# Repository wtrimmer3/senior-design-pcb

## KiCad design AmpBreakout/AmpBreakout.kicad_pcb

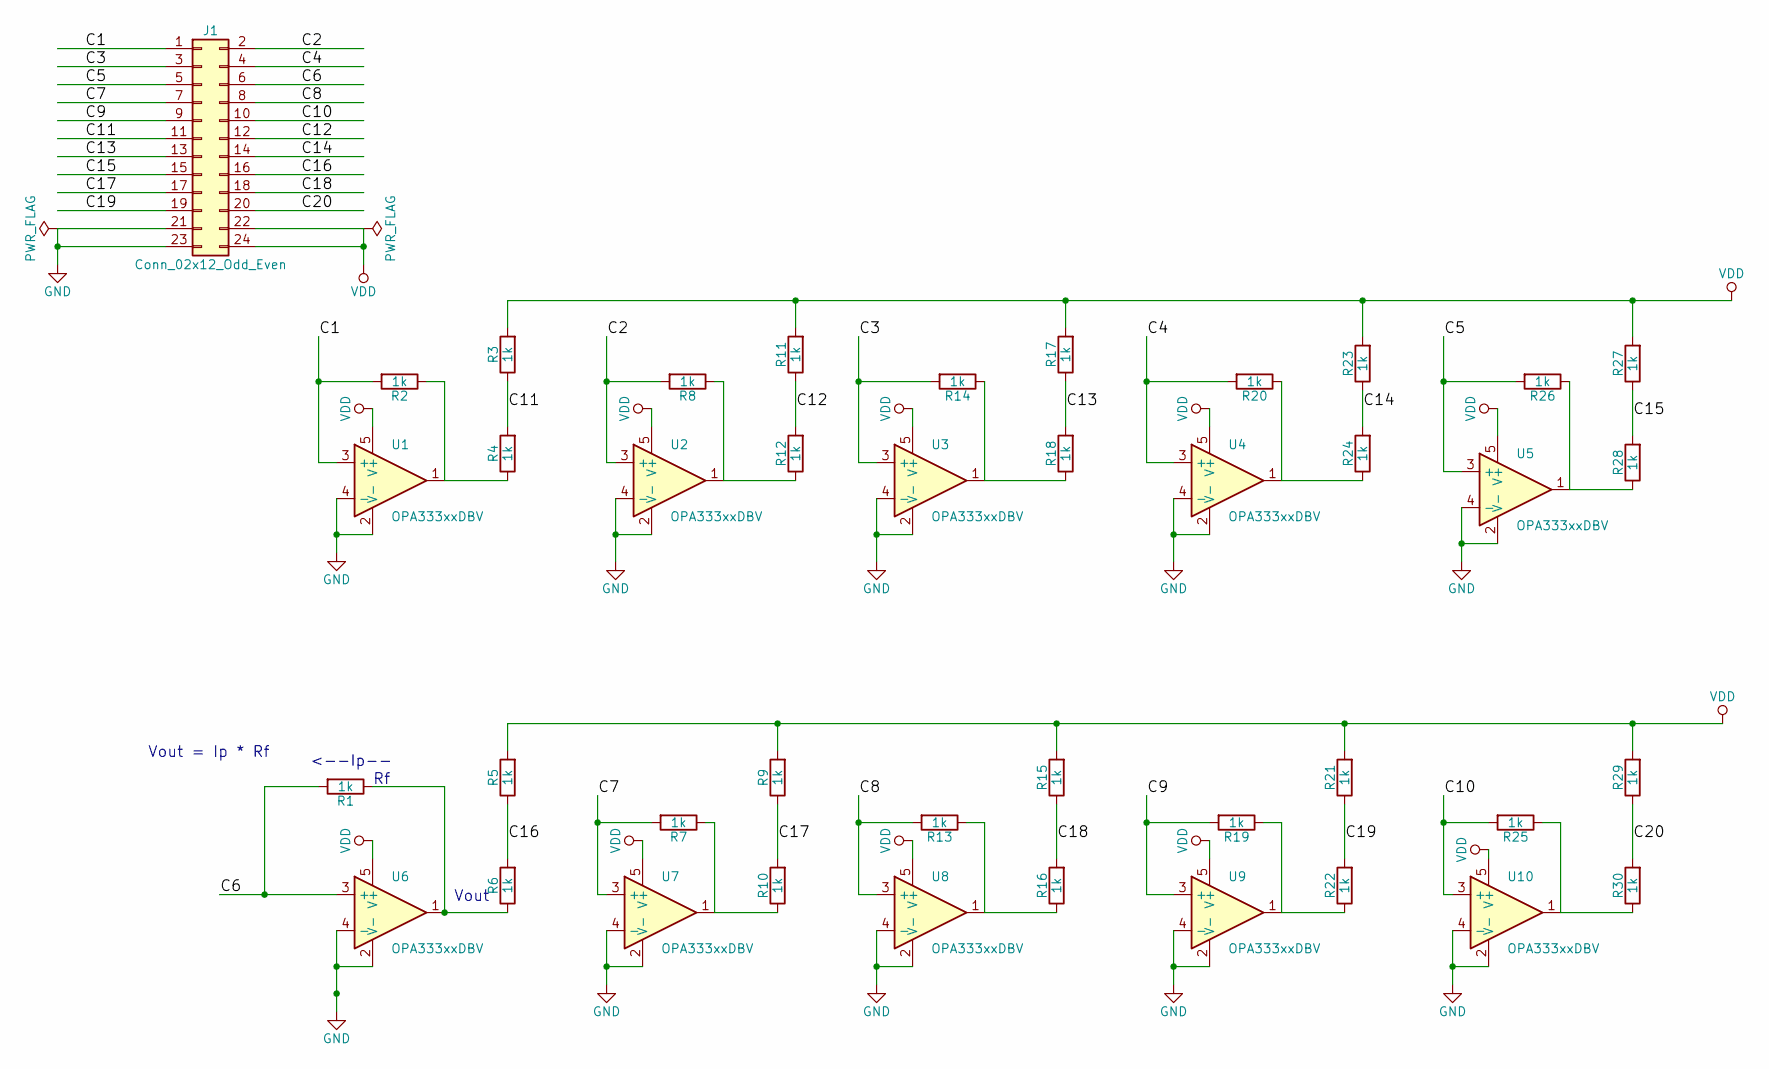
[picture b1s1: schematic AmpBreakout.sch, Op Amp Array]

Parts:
J1: Conn_02x12_Odd_Even; Pin_Header_Straight_2x12_Pitch1.00mm
R1, R2, R3, R4, R5, R6, R7, R8, R9, R10, R11, R12, R13, R14, R15, R16, R17, R18, R19, R20, R21, R22, R23, R24, R25, R26, R27, R28, R29, R30: 1k; R_1206
U1, U2, U3, U4, U5, U6, U7, U8, U9, U10: OPA333xxDBV; SOT-23-5

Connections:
/C1: J1.1, R2.2, U1.3 (+)
/C2: J1.2, R8.2, U2.3 (+)
/C3: J1.3, R14.2, U3.3 (+)
/C4: J1.4, R20.2, U4.3 (+)
/C5: J1.5, R26.2, U5.3 (+)
/C6: J1.6, R1.2, U6.3 (+)
/C7: J1.7, R7.2, U7.3 (+)
/C8: J1.8, R13.2, U8.3 (+)
/C9: J1.9, R19.2, U9.3 (+)
/C10: J1.10, R25.2, U10.3 (+)
/C11: J1.11, R3.1, R4.2
/C12: J1.12, R11.1, R12.2
/C13: J1.13, R17.1, R18.2
/C14: J1.14, R23.1, R24.2
/C15: J1.15, R27.1, R28.2
/C16: J1.16, R5.1, R6.2
/C17: J1.17, R9.1, R10.2
/C18: J1.18, R15.1, R16.2
/C19: J1.19, R21.1, R22.2
/C20: J1.20, R29.1, R30.2
GND: J1.21, J1.23, U1.2 (V-), U1.4 (-), U2.2 (V-), U2.4 (-), U3.2 (V-), U3.4 (-), U4.2 (V-), U4.4 (-), U5.2 (V-), U5.4 (-), U6.2 (V-), U6.4 (-), U7.2 (V-), U7.4 (-), U8.2 (V-), U8.4 (-), U9.2 (V-), U9.4 (-), U10.2 (V-), U10.4 (-)
unnamed: R1.1, R6.1, U6.1
unnamed: R2.1, R4.1, U1.1
unnamed: R7.1, R10.1, U7.1
unnamed: R8.1, R12.1, U2.1
unnamed: R13.1, R16.1, U8.1
unnamed: R14.1, R18.1, U3.1
unnamed: R19.1, R22.1, U9.1
unnamed: R20.1, R24.1, U4.1
unnamed: R25.1, R30.1, U10.1
unnamed: R26.1, R28.1, U5.1
VDD: J1.22, J1.24, R3.2, R5.2, R9.2, R11.2, R15.2, R17.2, R21.2, R23.2, R27.2, R29.2, U1.5 (V+), U2.5 (V+), U3.5 (V+), U4.5 (V+), U5.5 (V+), U6.5 (V+), U7.5 (V+), U8.5 (V+), U9.5 (V+), U10.5 (V+)

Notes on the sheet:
Vout = Ip * Rf
Vout
<--Ip--

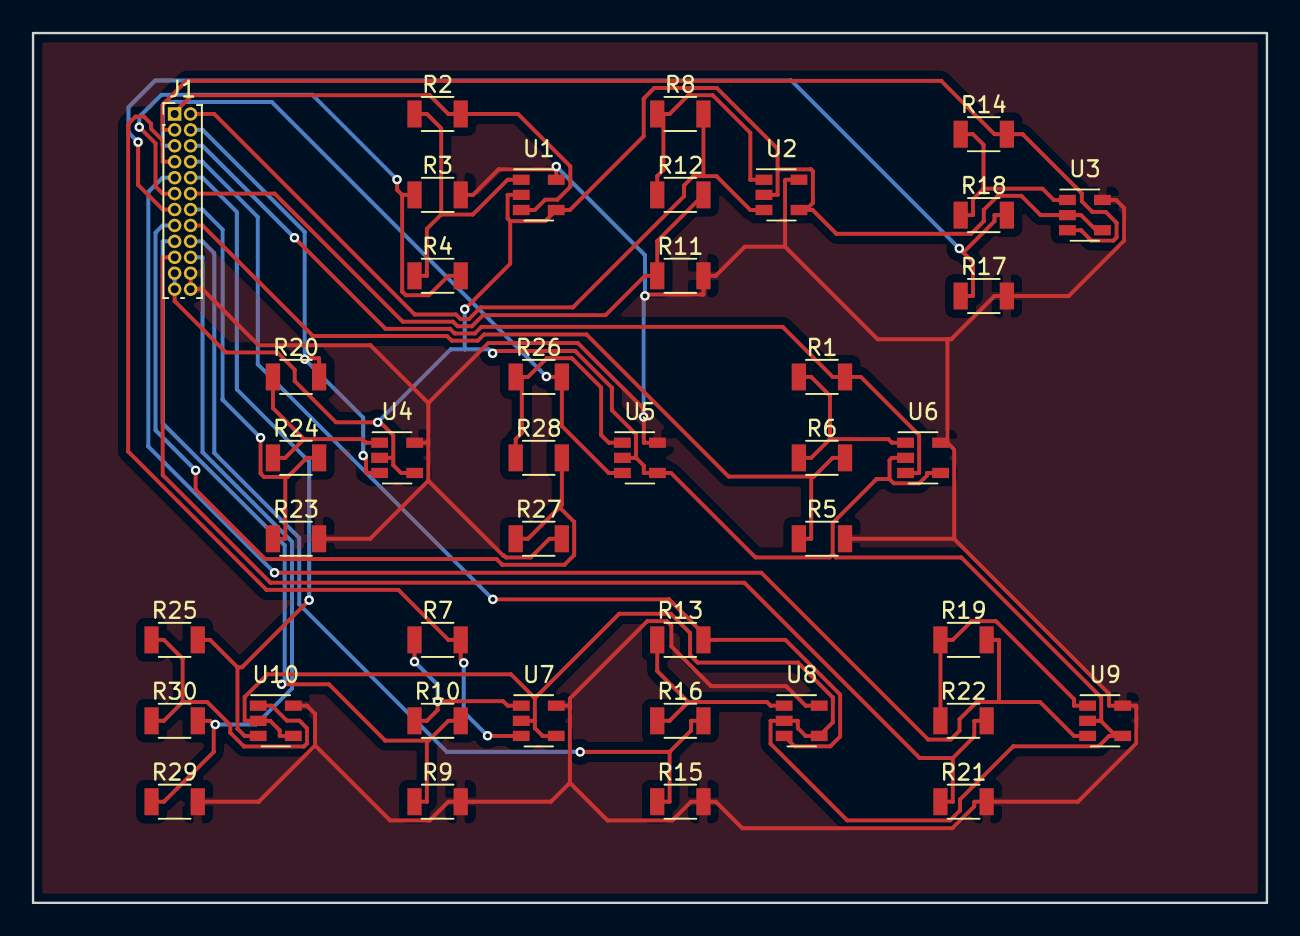
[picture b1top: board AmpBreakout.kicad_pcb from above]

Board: 2 copper layers, 77.5 x 54.6 mm, 41 parts (0 on the bottom side), 32 nets.

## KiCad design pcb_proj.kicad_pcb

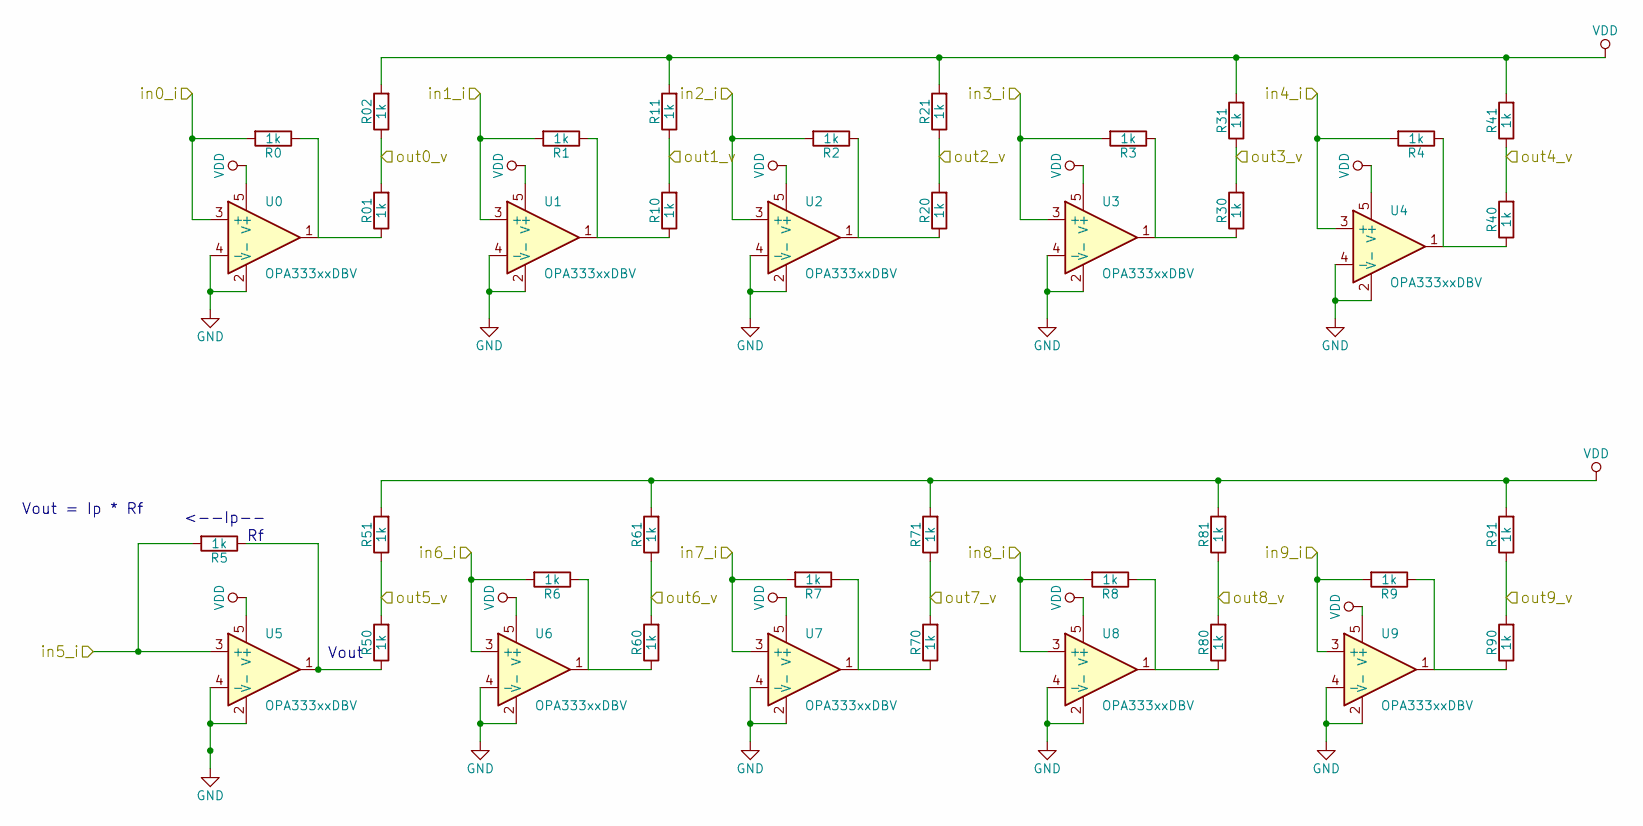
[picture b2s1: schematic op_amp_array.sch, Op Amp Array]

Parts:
R0, R1, R01, R2, R02, R3, R4, R5, R6, R7, R8, R9, R10, R11, R20, R21, R30, R31, R40, R41, R50, R51, R60, R61, R70, R71, R80, R81, R90, R91: 1k; R_1206
U0, U1, U2, U3, U4, U5, U6, U7, U8, U9: OPA333xxDBV; SOT-23-5

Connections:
/op_amps/out0_v: R01.2, R02.1; also elsewhere on the board
/op_amps/out1_v: R10.2, R11.1; also elsewhere on the board
/op_amps/out2_v: R20.2, R21.1; also elsewhere on the board
/op_amps/out3_v: R30.2, R31.1; also elsewhere on the board
/op_amps/out4_v: R40.2, R41.1; also elsewhere on the board
/op_amps/out5_v: R50.2, R51.1; also elsewhere on the board
/op_amps/out6_v: R60.2, R61.1; also elsewhere on the board
/op_amps/out7_v: R70.2, R71.1; also elsewhere on the board
/op_amps/out8_v: R80.2, R81.1; also elsewhere on the board
/op_amps/out9_v: R90.2, R91.1; also elsewhere on the board
/resistor_network/OUT0: R0.2, U0.3 (+); also elsewhere on the board
/resistor_network/OUT1: R1.2, U1.3 (+); also elsewhere on the board
/resistor_network/OUT2: R2.2, U2.3 (+); also elsewhere on the board
/resistor_network/OUT3: R3.2, U3.3 (+); also elsewhere on the board
/resistor_network/OUT4: R4.2, U4.3 (+); also elsewhere on the board
/resistor_network/OUT5: R5.2, U5.3 (+); also elsewhere on the board
/resistor_network/OUT6: R6.2, U6.3 (+); also elsewhere on the board
/resistor_network/OUT7: R7.2, U7.3 (+); also elsewhere on the board
/resistor_network/OUT8: R8.2, U8.3 (+); also elsewhere on the board
/resistor_network/OUT9: R9.2, U9.3 (+); also elsewhere on the board
GND: U0.2 (V-), U0.4 (-), U1.2 (V-), U1.4 (-), U2.2 (V-), U2.4 (-), U3.2 (V-), U3.4 (-), U4.2 (V-), U4.4 (-), U5.2 (V-), U5.4 (-), U6.2 (V-), U6.4 (-), U7.2 (V-), U7.4 (-), U8.2 (V-), U8.4 (-), U9.2 (V-), U9.4 (-); also elsewhere on the board
unnamed: R0.1, R01.1, U0.1
unnamed: R1.1, R10.1, U1.1
unnamed: R2.1, R20.1, U2.1
unnamed: R3.1, R30.1, U3.1
unnamed: R4.1, R40.1, U4.1
unnamed: R5.1, R50.1, U5.1
unnamed: R6.1, R60.1, U6.1
unnamed: R7.1, R70.1, U7.1
unnamed: R8.1, R80.1, U8.1
unnamed: R9.1, R90.1, U9.1
VDD: R02.2, R11.2, R21.2, R31.2, R41.2, R51.2, R61.2, R71.2, R81.2, R91.2, U0.5 (V+), U1.5 (V+), U2.5 (V+), U3.5 (V+), U4.5 (V+), U5.5 (V+), U6.5 (V+), U7.5 (V+), U8.5 (V+), U9.5 (V+); also elsewhere on the board

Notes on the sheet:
Vout = Ip * Rf
Vout
<--Ip--

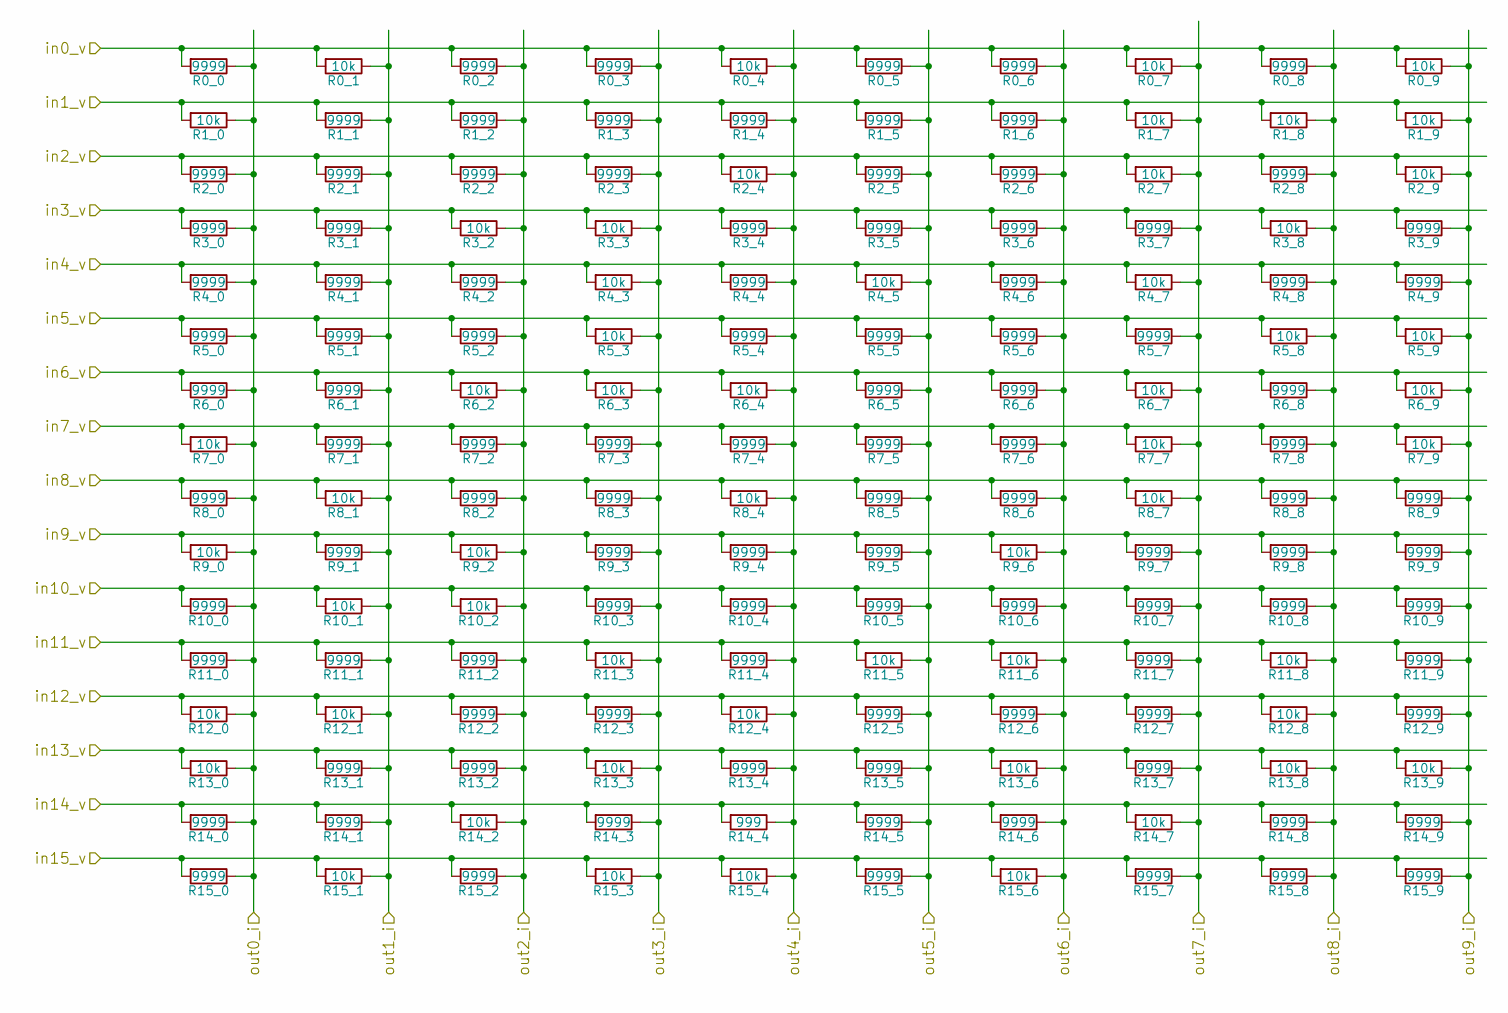
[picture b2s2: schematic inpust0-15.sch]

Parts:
R0_0, R0_2, R0_3, R0_5, R0_6, R0_8, R1_1, R1_2, R1_3, R1_4, R1_5, R1_6, R2_0, R2_1, R2_2, R2_3, R2_5, R2_6, R2_8, R3_0, R3_1, R3_4, R3_5, R3_6, R3_7, R3_9, R4_0, R4_1, R4_2, R4_4, R4_6, R4_8, R4_9, R5_0, R5_1, R5_2, R5_4, R5_5, R5_6, R5_7, R6_0, R6_1, R6_5, R6_6, R6_8, R7_1, R7_2, R7_3, R7_4, R7_5, R7_6, R7_8, R8_0, R8_2, R8_3, R8_5, R8_6, R8_8, R8_9, R9_1, R9_3, R9_4, R9_5, R9_7, R9_8, R9_9, R10_0, R10_3, R10_4, R10_5, R10_6, R10_7, R10_8, R10_9, R11_0, R11_1, R11_2, R11_4, R11_7, R11_9, R12_2, R12_3, R12_5, R12_6, R12_7, R12_9, R13_1, R13_2, R13_4, R13_5, R13_7, R14_0, R14_1, R14_3, R14_5, R14_6, R14_8, R14_9, R15_0, R15_2, R15_5, R15_7, R15_8, R15_9: 9999; R_1206
R0_1, R0_4, R0_7, R0_9, R1_0, R1_7, R1_8, R1_9, R2_4, R2_7, R2_9, R3_2, R3_3, R3_8, R4_3, R4_5, R4_7, R5_3, R5_8, R5_9, R6_2, R6_3, R6_4, R6_7, R6_9, R7_0, R7_7, R7_9, R8_1, R8_4, R8_7, R9_0, R9_2, R9_6, R10_1, R10_2, R11_3, R11_5, R11_6, R11_8, R12_0, R12_1, R12_4, R12_8, R13_0, R13_3, R13_6, R13_8, R13_9, R14_2, R14_7, R15_1, R15_3, R15_4, R15_6: 10k; R_1206
R14_4: 999; R_1206

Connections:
/C0: R0_0.2, R0_1.2, R0_2.2, R0_3.2, R0_4.2, R0_5.2, R0_6.2, R0_7.2, R0_8.2, R0_9.2; also elsewhere on the board
/C1: R1_0.2, R1_1.2, R1_2.2, R1_3.2, R1_4.2, R1_5.2, R1_6.2, R1_7.2, R1_8.2, R1_9.2; also elsewhere on the board
/C2: R2_0.2, R2_1.2, R2_2.2, R2_3.2, R2_4.2, R2_5.2, R2_6.2, R2_7.2, R2_8.2, R2_9.2; also elsewhere on the board
/C3: R3_0.2, R3_1.2, R3_2.2, R3_3.2, R3_4.2, R3_5.2, R3_6.2, R3_7.2, R3_8.2, R3_9.2; also elsewhere on the board
/C4: R4_0.2, R4_1.2, R4_2.2, R4_3.2, R4_4.2, R4_5.2, R4_6.2, R4_7.2, R4_8.2, R4_9.2; also elsewhere on the board
/C5: R5_0.2, R5_1.2, R5_2.2, R5_3.2, R5_4.2, R5_5.2, R5_6.2, R5_7.2, R5_8.2, R5_9.2; also elsewhere on the board
/C6: R6_0.2, R6_1.2, R6_2.2, R6_3.2, R6_4.2, R6_5.2, R6_6.2, R6_7.2, R6_8.2, R6_9.2; also elsewhere on the board
/C7: R7_0.2, R7_1.2, R7_2.2, R7_3.2, R7_4.2, R7_5.2, R7_6.2, R7_7.2, R7_8.2, R7_9.2; also elsewhere on the board
/C8: R8_0.2, R8_1.2, R8_2.2, R8_3.2, R8_4.2, R8_5.2, R8_6.2, R8_7.2, R8_8.2, R8_9.2; also elsewhere on the board
/C9: R9_0.2, R9_1.2, R9_2.2, R9_3.2, R9_4.2, R9_5.2, R9_6.2, R9_7.2, R9_8.2, R9_9.2; also elsewhere on the board
/C10: R10_0.2, R10_1.2, R10_2.2, R10_3.2, R10_4.2, R10_5.2, R10_6.2, R10_7.2, R10_8.2, R10_9.2; also elsewhere on the board
/C11: R11_0.2, R11_1.2, R11_2.2, R11_3.2, R11_4.2, R11_5.2, R11_6.2, R11_7.2, R11_8.2, R11_9.2; also elsewhere on the board
/C12: R12_0.2, R12_1.2, R12_2.2, R12_3.2, R12_4.2, R12_5.2, R12_6.2, R12_7.2, R12_8.2, R12_9.2; also elsewhere on the board
/C13: R13_0.2, R13_1.2, R13_2.2, R13_3.2, R13_4.2, R13_5.2, R13_6.2, R13_7.2, R13_8.2, R13_9.2; also elsewhere on the board
/C14: R14_0.2, R14_1.2, R14_2.2, R14_3.2, R14_4.2, R14_5.2, R14_6.2, R14_7.2, R14_8.2, R14_9.2; also elsewhere on the board
/C15: R15_0.2, R15_1.2, R15_2.2, R15_3.2, R15_4.2, R15_5.2, R15_6.2, R15_7.2, R15_8.2, R15_9.2; also elsewhere on the board
/resistor_network/OUT0: R0_0.1, R1_0.1, R2_0.1, R3_0.1, R4_0.1, R5_0.1, R6_0.1, R7_0.1, R8_0.1, R9_0.1, R10_0.1, R11_0.1, R12_0.1, R13_0.1, R14_0.1, R15_0.1; also elsewhere on the board
/resistor_network/OUT1: R0_1.1, R1_1.1, R2_1.1, R3_1.1, R4_1.1, R5_1.1, R6_1.1, R7_1.1, R8_1.1, R9_1.1, R10_1.1, R11_1.1, R12_1.1, R13_1.1, R14_1.1, R15_1.1; also elsewhere on the board
/resistor_network/OUT2: R0_2.1, R1_2.1, R2_2.1, R3_2.1, R4_2.1, R5_2.1, R6_2.1, R7_2.1, R8_2.1, R9_2.1, R10_2.1, R11_2.1, R12_2.1, R13_2.1, R14_2.1, R15_2.1; also elsewhere on the board
/resistor_network/OUT3: R0_3.1, R1_3.1, R2_3.1, R3_3.1, R4_3.1, R5_3.1, R6_3.1, R7_3.1, R8_3.1, R9_3.1, R10_3.1, R11_3.1, R12_3.1, R13_3.1, R14_3.1, R15_3.1; also elsewhere on the board
/resistor_network/OUT4: R0_4.1, R1_4.1, R2_4.1, R3_4.1, R4_4.1, R5_4.1, R6_4.1, R7_4.1, R8_4.1, R9_4.1, R10_4.1, R11_4.1, R12_4.1, R13_4.1, R14_4.1, R15_4.1; also elsewhere on the board
/resistor_network/OUT5: R0_5.1, R1_5.1, R2_5.1, R3_5.1, R4_5.1, R5_5.1, R6_5.1, R7_5.1, R8_5.1, R9_5.1, R10_5.1, R11_5.1, R12_5.1, R13_5.1, R14_5.1, R15_5.1; also elsewhere on the board
/resistor_network/OUT6: R0_6.1, R1_6.1, R2_6.1, R3_6.1, R4_6.1, R5_6.1, R6_6.1, R7_6.1, R8_6.1, R9_6.1, R10_6.1, R11_6.1, R12_6.1, R13_6.1, R14_6.1, R15_6.1; also elsewhere on the board
/resistor_network/OUT7: R0_7.1, R1_7.1, R2_7.1, R3_7.1, R4_7.1, R5_7.1, R6_7.1, R7_7.1, R8_7.1, R9_7.1, R10_7.1, R11_7.1, R12_7.1, R13_7.1, R14_7.1, R15_7.1; also elsewhere on the board
/resistor_network/OUT8: R0_8.1, R1_8.1, R2_8.1, R3_8.1, R4_8.1, R5_8.1, R6_8.1, R7_8.1, R8_8.1, R9_8.1, R10_8.1, R11_8.1, R12_8.1, R13_8.1, R14_8.1, R15_8.1; also elsewhere on the board
/resistor_network/OUT9: R0_9.1, R1_9.1, R2_9.1, R3_9.1, R4_9.1, R5_9.1, R6_9.1, R7_9.1, R8_9.1, R9_9.1, R10_9.1, R11_9.1, R12_9.1, R13_9.1, R14_9.1, R15_9.1; also elsewhere on the board

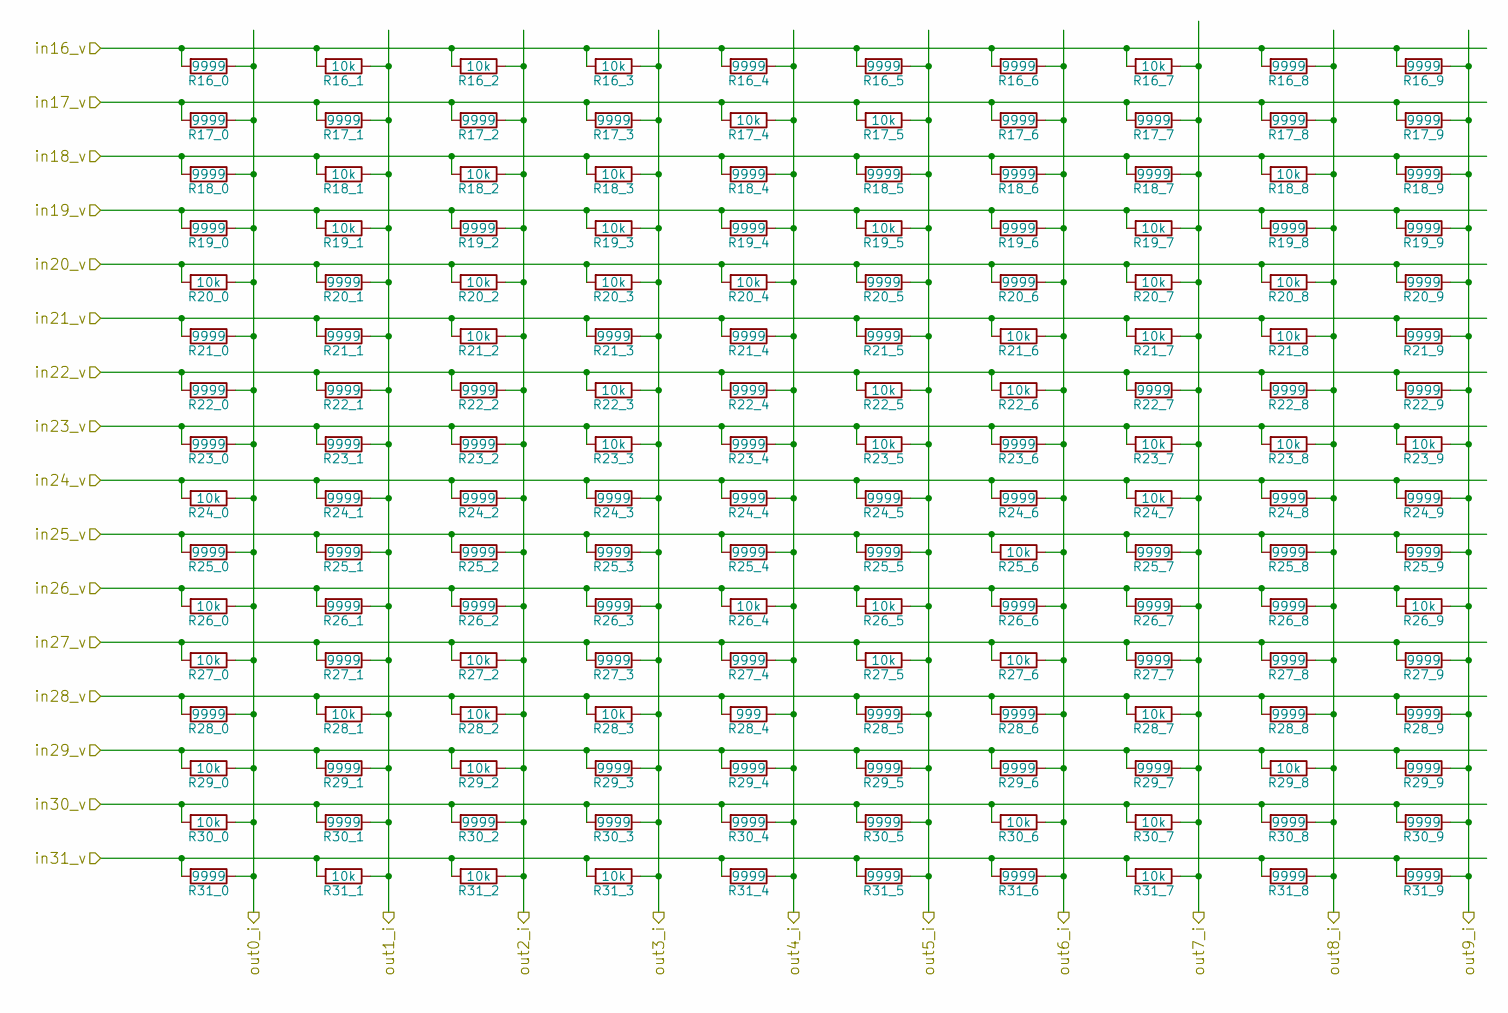
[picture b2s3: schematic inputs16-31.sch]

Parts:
R16_0, R16_4, R16_5, R16_6, R16_8, R16_9, R17_0, R17_1, R17_2, R17_3, R17_6, R17_7, R17_8, R17_9, R18_0, R18_4, R18_5, R18_6, R18_7, R18_9, R19_0, R19_2, R19_4, R19_6, R19_8, R19_9, R20_1, R20_5, R20_6, R20_9, R21_0, R21_1, R21_3, R21_4, R21_5, R21_9, R22_0, R22_1, R22_2, R22_4, R22_7, R22_8, R22_9, R23_0, R23_1, R23_2, R23_4, R23_6, R24_1, R24_2, R24_3, R24_4, R24_5, R24_6, R24_8, R24_9, R25_0, R25_1, R25_2, R25_3, R25_4, R25_5, R25_7, R25_8, R25_9, R26_1, R26_2, R26_3, R26_6, R26_7, R26_8, R27_1, R27_3, R27_4, R27_7, R27_8, R27_9, R28_0, R28_5, R28_6, R28_8, R28_9, R29_1, R29_3, R29_4, R29_5, R29_6, R29_7, R29_9, R30_1, R30_2, R30_3, R30_4, R30_5, R30_8, R30_9, R31_0, R31_4, R31_5, R31_6, R31_8, R31_9: 9999; R_1206
R16_1, R16_2, R16_3, R16_7, R17_4, R17_5, R18_1, R18_2, R18_3, R18_8, R19_1, R19_3, R19_5, R19_7, R20_0, R20_2, R20_3, R20_4, R20_7, R20_8, R21_2, R21_6, R21_7, R21_8, R22_3, R22_5, R22_6, R23_3, R23_5, R23_7, R23_8, R23_9, R24_0, R24_7, R25_6, R26_0, R26_4, R26_5, R26_9, R27_0, R27_2, R27_5, R27_6, R28_1, R28_2, R28_3, R28_7, R29_0, R29_2, R29_8, R30_0, R30_6, R30_7, R31_1, R31_2, R31_3, R31_7: 10k; R_1206
R28_4: 999; R_1206

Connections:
/C16: R16_0.2, R16_1.2, R16_2.2, R16_3.2, R16_4.2, R16_5.2, R16_6.2, R16_7.2, R16_8.2, R16_9.2; also elsewhere on the board
/C17: R17_0.2, R17_1.2, R17_2.2, R17_3.2, R17_4.2, R17_5.2, R17_6.2, R17_7.2, R17_8.2, R17_9.2; also elsewhere on the board
/C18: R18_0.2, R18_1.2, R18_2.2, R18_3.2, R18_4.2, R18_5.2, R18_6.2, R18_7.2, R18_8.2, R18_9.2; also elsewhere on the board
/C19: R19_0.2, R19_1.2, R19_2.2, R19_3.2, R19_4.2, R19_5.2, R19_6.2, R19_7.2, R19_8.2, R19_9.2; also elsewhere on the board
/C20: R20_0.2, R20_1.2, R20_2.2, R20_3.2, R20_4.2, R20_5.2, R20_6.2, R20_7.2, R20_8.2, R20_9.2; also elsewhere on the board
/C21: R21_0.2, R21_1.2, R21_2.2, R21_3.2, R21_4.2, R21_5.2, R21_6.2, R21_7.2, R21_8.2, R21_9.2; also elsewhere on the board
/C22: R22_0.2, R22_1.2, R22_2.2, R22_3.2, R22_4.2, R22_5.2, R22_6.2, R22_7.2, R22_8.2, R22_9.2; also elsewhere on the board
/C23: R23_0.2, R23_1.2, R23_2.2, R23_3.2, R23_4.2, R23_5.2, R23_6.2, R23_7.2, R23_8.2, R23_9.2; also elsewhere on the board
/C24: R24_0.2, R24_1.2, R24_2.2, R24_3.2, R24_4.2, R24_5.2, R24_6.2, R24_7.2, R24_8.2, R24_9.2; also elsewhere on the board
/C25: R25_0.2, R25_1.2, R25_2.2, R25_3.2, R25_4.2, R25_5.2, R25_6.2, R25_7.2, R25_8.2, R25_9.2; also elsewhere on the board
/C26: R26_0.2, R26_1.2, R26_2.2, R26_3.2, R26_4.2, R26_5.2, R26_6.2, R26_7.2, R26_8.2, R26_9.2; also elsewhere on the board
/C27: R27_0.2, R27_1.2, R27_2.2, R27_3.2, R27_4.2, R27_5.2, R27_6.2, R27_7.2, R27_8.2, R27_9.2; also elsewhere on the board
/C28: R28_0.2, R28_1.2, R28_2.2, R28_3.2, R28_4.2, R28_5.2, R28_6.2, R28_7.2, R28_8.2, R28_9.2; also elsewhere on the board
/C29: R29_0.2, R29_1.2, R29_2.2, R29_3.2, R29_4.2, R29_5.2, R29_6.2, R29_7.2, R29_8.2, R29_9.2; also elsewhere on the board
/C30: R30_0.2, R30_1.2, R30_2.2, R30_3.2, R30_4.2, R30_5.2, R30_6.2, R30_7.2, R30_8.2, R30_9.2; also elsewhere on the board
/C31: R31_0.2, R31_1.2, R31_2.2, R31_3.2, R31_4.2, R31_5.2, R31_6.2, R31_7.2, R31_8.2, R31_9.2; also elsewhere on the board
/resistor_network/OUT0: R16_0.1, R17_0.1, R18_0.1, R19_0.1, R20_0.1, R21_0.1, R22_0.1, R23_0.1, R24_0.1, R25_0.1, R26_0.1, R27_0.1, R28_0.1, R29_0.1, R30_0.1, R31_0.1; also elsewhere on the board
/resistor_network/OUT1: R16_1.1, R17_1.1, R18_1.1, R19_1.1, R20_1.1, R21_1.1, R22_1.1, R23_1.1, R24_1.1, R25_1.1, R26_1.1, R27_1.1, R28_1.1, R29_1.1, R30_1.1, R31_1.1; also elsewhere on the board
/resistor_network/OUT2: R16_2.1, R17_2.1, R18_2.1, R19_2.1, R20_2.1, R21_2.1, R22_2.1, R23_2.1, R24_2.1, R25_2.1, R26_2.1, R27_2.1, R28_2.1, R29_2.1, R30_2.1, R31_2.1; also elsewhere on the board
/resistor_network/OUT3: R16_3.1, R17_3.1, R18_3.1, R19_3.1, R20_3.1, R21_3.1, R22_3.1, R23_3.1, R24_3.1, R25_3.1, R26_3.1, R27_3.1, R28_3.1, R29_3.1, R30_3.1, R31_3.1; also elsewhere on the board
/resistor_network/OUT4: R16_4.1, R17_4.1, R18_4.1, R19_4.1, R20_4.1, R21_4.1, R22_4.1, R23_4.1, R24_4.1, R25_4.1, R26_4.1, R27_4.1, R28_4.1, R29_4.1, R30_4.1, R31_4.1; also elsewhere on the board
/resistor_network/OUT5: R16_5.1, R17_5.1, R18_5.1, R19_5.1, R20_5.1, R21_5.1, R22_5.1, R23_5.1, R24_5.1, R25_5.1, R26_5.1, R27_5.1, R28_5.1, R29_5.1, R30_5.1, R31_5.1; also elsewhere on the board
/resistor_network/OUT6: R16_6.1, R17_6.1, R18_6.1, R19_6.1, R20_6.1, R21_6.1, R22_6.1, R23_6.1, R24_6.1, R25_6.1, R26_6.1, R27_6.1, R28_6.1, R29_6.1, R30_6.1, R31_6.1; also elsewhere on the board
/resistor_network/OUT7: R16_7.1, R17_7.1, R18_7.1, R19_7.1, R20_7.1, R21_7.1, R22_7.1, R23_7.1, R24_7.1, R25_7.1, R26_7.1, R27_7.1, R28_7.1, R29_7.1, R30_7.1, R31_7.1; also elsewhere on the board
/resistor_network/OUT8: R16_8.1, R17_8.1, R18_8.1, R19_8.1, R20_8.1, R21_8.1, R22_8.1, R23_8.1, R24_8.1, R25_8.1, R26_8.1, R27_8.1, R28_8.1, R29_8.1, R30_8.1, R31_8.1; also elsewhere on the board
/resistor_network/OUT9: R16_9.1, R17_9.1, R18_9.1, R19_9.1, R20_9.1, R21_9.1, R22_9.1, R23_9.1, R24_9.1, R25_9.1, R26_9.1, R27_9.1, R28_9.1, R29_9.1, R30_9.1, R31_9.1; also elsewhere on the board

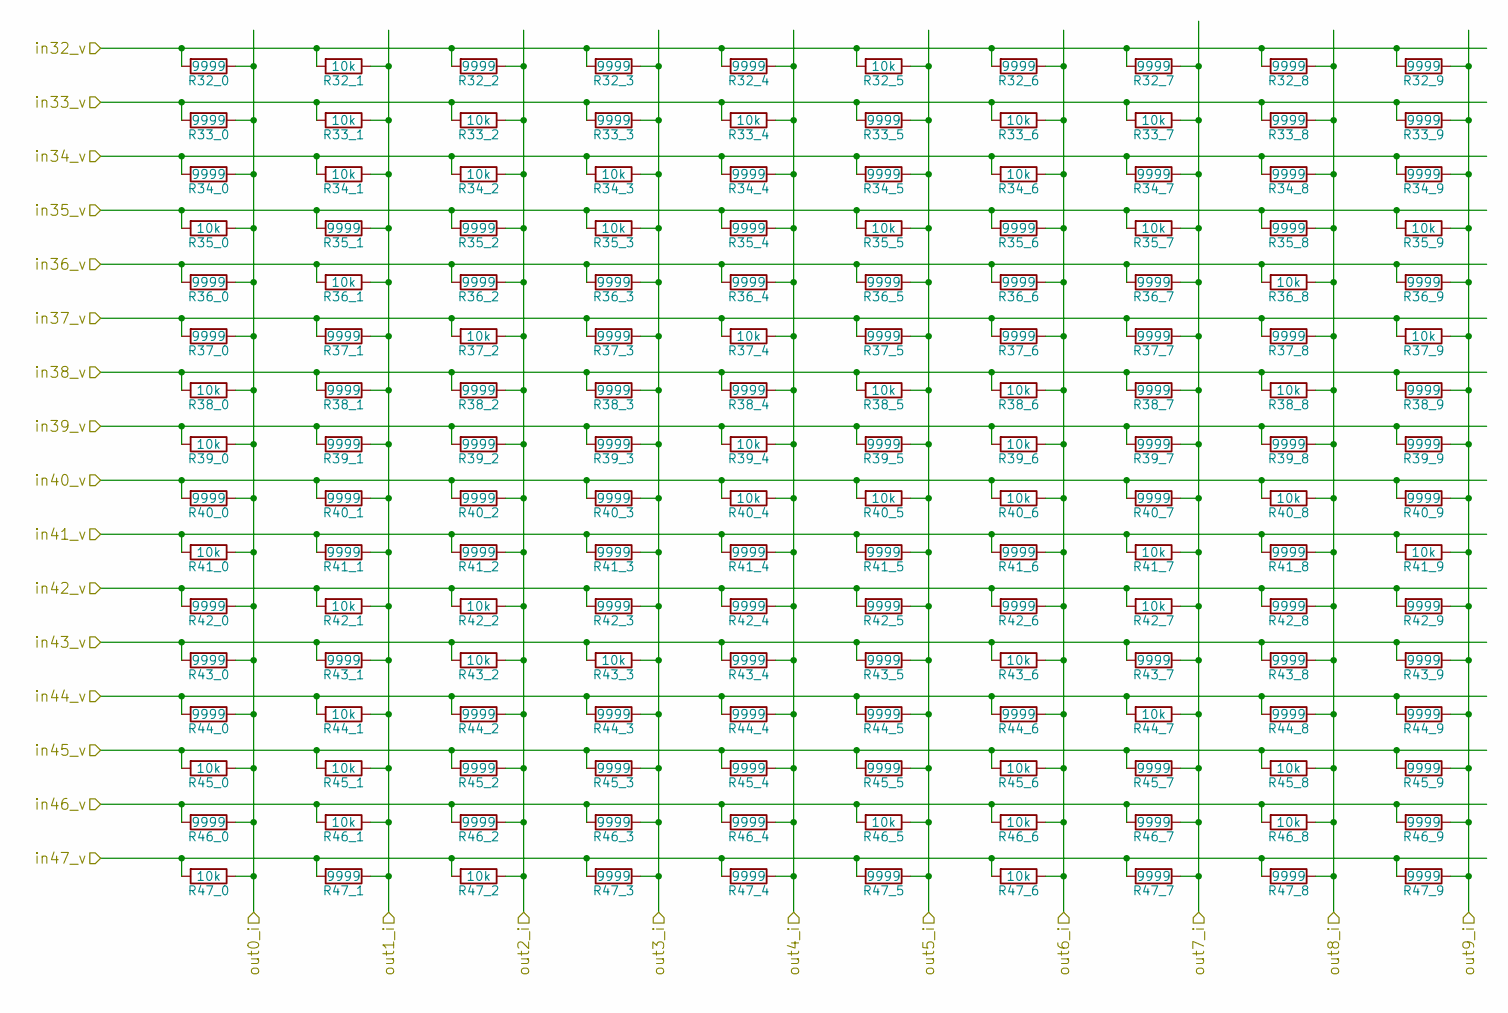
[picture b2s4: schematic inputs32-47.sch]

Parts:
R32_0, R32_2, R32_3, R32_4, R32_6, R32_7, R32_8, R32_9, R33_0, R33_3, R33_5, R33_8, R33_9, R34_0, R34_4, R34_5, R34_7, R34_8, R34_9, R35_1, R35_2, R35_4, R35_6, R35_8, R36_0, R36_2, R36_3, R36_4, R36_5, R36_6, R36_7, R36_9, R37_0, R37_1, R37_3, R37_5, R37_6, R37_7, R37_8, R38_1, R38_2, R38_3, R38_4, R38_7, R38_9, R39_1, R39_2, R39_3, R39_5, R39_7, R39_8, R39_9, R40_0, R40_1, R40_2, R40_3, R40_7, R40_9, R41_1, R41_2, R41_3, R41_4, R41_5, R41_6, R41_8, R42_0, R42_3, R42_4, R42_5, R42_6, R42_8, R42_9, R43_0, R43_1, R43_4, R43_5, R43_7, R43_8, R43_9, R44_0, R44_2, R44_3, R44_4, R44_5, R44_6, R44_8, R44_9, R45_2, R45_3, R45_4, R45_5, R45_7, R45_9, R46_0, R46_2, R46_3, R46_4, R46_7, R46_9, R47_1, R47_3, R47_4, R47_5, R47_7, R47_8, R47_9: 9999; R_1206
R32_1, R32_5, R33_1, R33_2, R33_4, R33_6, R33_7, R34_1, R34_2, R34_3, R34_6, R35_0, R35_3, R35_5, R35_7, R35_9, R36_1, R36_8, R37_2, R37_4, R37_9, R38_0, R38_5, R38_6, R38_8, R39_0, R39_4, R39_6, R40_4, R40_5, R40_6, R40_8, R41_0, R41_7, R41_9, R42_1, R42_2, R42_7, R43_2, R43_3, R43_6, R44_1, R44_7, R45_0, R45_1, R45_6, R45_8, R46_1, R46_5, R46_6, R46_8, R47_0, R47_2, R47_6: 10k; R_1206

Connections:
/C32: R32_0.2, R32_1.2, R32_2.2, R32_3.2, R32_4.2, R32_5.2, R32_6.2, R32_7.2, R32_8.2, R32_9.2; also elsewhere on the board
/C33: R33_0.2, R33_1.2, R33_2.2, R33_3.2, R33_4.2, R33_5.2, R33_6.2, R33_7.2, R33_8.2, R33_9.2; also elsewhere on the board
/C34: R34_0.2, R34_1.2, R34_2.2, R34_3.2, R34_4.2, R34_5.2, R34_6.2, R34_7.2, R34_8.2, R34_9.2; also elsewhere on the board
/C35: R35_0.2, R35_1.2, R35_2.2, R35_3.2, R35_4.2, R35_5.2, R35_6.2, R35_7.2, R35_8.2, R35_9.2; also elsewhere on the board
/C36: R36_0.2, R36_1.2, R36_2.2, R36_3.2, R36_4.2, R36_5.2, R36_6.2, R36_7.2, R36_8.2, R36_9.2; also elsewhere on the board
/C37: R37_0.2, R37_1.2, R37_2.2, R37_3.2, R37_4.2, R37_5.2, R37_6.2, R37_7.2, R37_8.2, R37_9.2; also elsewhere on the board
/C38: R38_0.2, R38_1.2, R38_2.2, R38_3.2, R38_4.2, R38_5.2, R38_6.2, R38_7.2, R38_8.2, R38_9.2; also elsewhere on the board
/C39: R39_0.2, R39_1.2, R39_2.2, R39_3.2, R39_4.2, R39_5.2, R39_6.2, R39_7.2, R39_8.2, R39_9.2; also elsewhere on the board
/C40: R40_0.2, R40_1.2, R40_2.2, R40_3.2, R40_4.2, R40_5.2, R40_6.2, R40_7.2, R40_8.2, R40_9.2; also elsewhere on the board
/C41: R41_0.2, R41_1.2, R41_2.2, R41_3.2, R41_4.2, R41_5.2, R41_6.2, R41_7.2, R41_8.2, R41_9.2; also elsewhere on the board
/C42: R42_0.2, R42_1.2, R42_2.2, R42_3.2, R42_4.2, R42_5.2, R42_6.2, R42_7.2, R42_8.2, R42_9.2; also elsewhere on the board
/C43: R43_0.2, R43_1.2, R43_2.2, R43_3.2, R43_4.2, R43_5.2, R43_6.2, R43_7.2, R43_8.2, R43_9.2; also elsewhere on the board
/C44: R44_0.2, R44_1.2, R44_2.2, R44_3.2, R44_4.2, R44_5.2, R44_6.2, R44_7.2, R44_8.2, R44_9.2; also elsewhere on the board
/C45: R45_0.2, R45_1.2, R45_2.2, R45_3.2, R45_4.2, R45_5.2, R45_6.2, R45_7.2, R45_8.2, R45_9.2; also elsewhere on the board
/C46: R46_0.2, R46_1.2, R46_2.2, R46_3.2, R46_4.2, R46_5.2, R46_6.2, R46_7.2, R46_8.2, R46_9.2; also elsewhere on the board
/C47: R47_0.2, R47_1.2, R47_2.2, R47_3.2, R47_4.2, R47_5.2, R47_6.2, R47_7.2, R47_8.2, R47_9.2; also elsewhere on the board
/resistor_network/OUT0: R32_0.1, R33_0.1, R34_0.1, R35_0.1, R36_0.1, R37_0.1, R38_0.1, R39_0.1, R40_0.1, R41_0.1, R42_0.1, R43_0.1, R44_0.1, R45_0.1, R46_0.1, R47_0.1; also elsewhere on the board
/resistor_network/OUT1: R32_1.1, R33_1.1, R34_1.1, R35_1.1, R36_1.1, R37_1.1, R38_1.1, R39_1.1, R40_1.1, R41_1.1, R42_1.1, R43_1.1, R44_1.1, R45_1.1, R46_1.1, R47_1.1; also elsewhere on the board
/resistor_network/OUT2: R32_2.1, R33_2.1, R34_2.1, R35_2.1, R36_2.1, R37_2.1, R38_2.1, R39_2.1, R40_2.1, R41_2.1, R42_2.1, R43_2.1, R44_2.1, R45_2.1, R46_2.1, R47_2.1; also elsewhere on the board
/resistor_network/OUT3: R32_3.1, R33_3.1, R34_3.1, R35_3.1, R36_3.1, R37_3.1, R38_3.1, R39_3.1, R40_3.1, R41_3.1, R42_3.1, R43_3.1, R44_3.1, R45_3.1, R46_3.1, R47_3.1; also elsewhere on the board
/resistor_network/OUT4: R32_4.1, R33_4.1, R34_4.1, R35_4.1, R36_4.1, R37_4.1, R38_4.1, R39_4.1, R40_4.1, R41_4.1, R42_4.1, R43_4.1, R44_4.1, R45_4.1, R46_4.1, R47_4.1; also elsewhere on the board
/resistor_network/OUT5: R32_5.1, R33_5.1, R34_5.1, R35_5.1, R36_5.1, R37_5.1, R38_5.1, R39_5.1, R40_5.1, R41_5.1, R42_5.1, R43_5.1, R44_5.1, R45_5.1, R46_5.1, R47_5.1; also elsewhere on the board
/resistor_network/OUT6: R32_6.1, R33_6.1, R34_6.1, R35_6.1, R36_6.1, R37_6.1, R38_6.1, R39_6.1, R40_6.1, R41_6.1, R42_6.1, R43_6.1, R44_6.1, R45_6.1, R46_6.1, R47_6.1; also elsewhere on the board
/resistor_network/OUT7: R32_7.1, R33_7.1, R34_7.1, R35_7.1, R36_7.1, R37_7.1, R38_7.1, R39_7.1, R40_7.1, R41_7.1, R42_7.1, R43_7.1, R44_7.1, R45_7.1, R46_7.1, R47_7.1; also elsewhere on the board
/resistor_network/OUT8: R32_8.1, R33_8.1, R34_8.1, R35_8.1, R36_8.1, R37_8.1, R38_8.1, R39_8.1, R40_8.1, R41_8.1, R42_8.1, R43_8.1, R44_8.1, R45_8.1, R46_8.1, R47_8.1; also elsewhere on the board
/resistor_network/OUT9: R32_9.1, R33_9.1, R34_9.1, R35_9.1, R36_9.1, R37_9.1, R38_9.1, R39_9.1, R40_9.1, R41_9.1, R42_9.1, R43_9.1, R44_9.1, R45_9.1, R46_9.1, R47_9.1; also elsewhere on the board
